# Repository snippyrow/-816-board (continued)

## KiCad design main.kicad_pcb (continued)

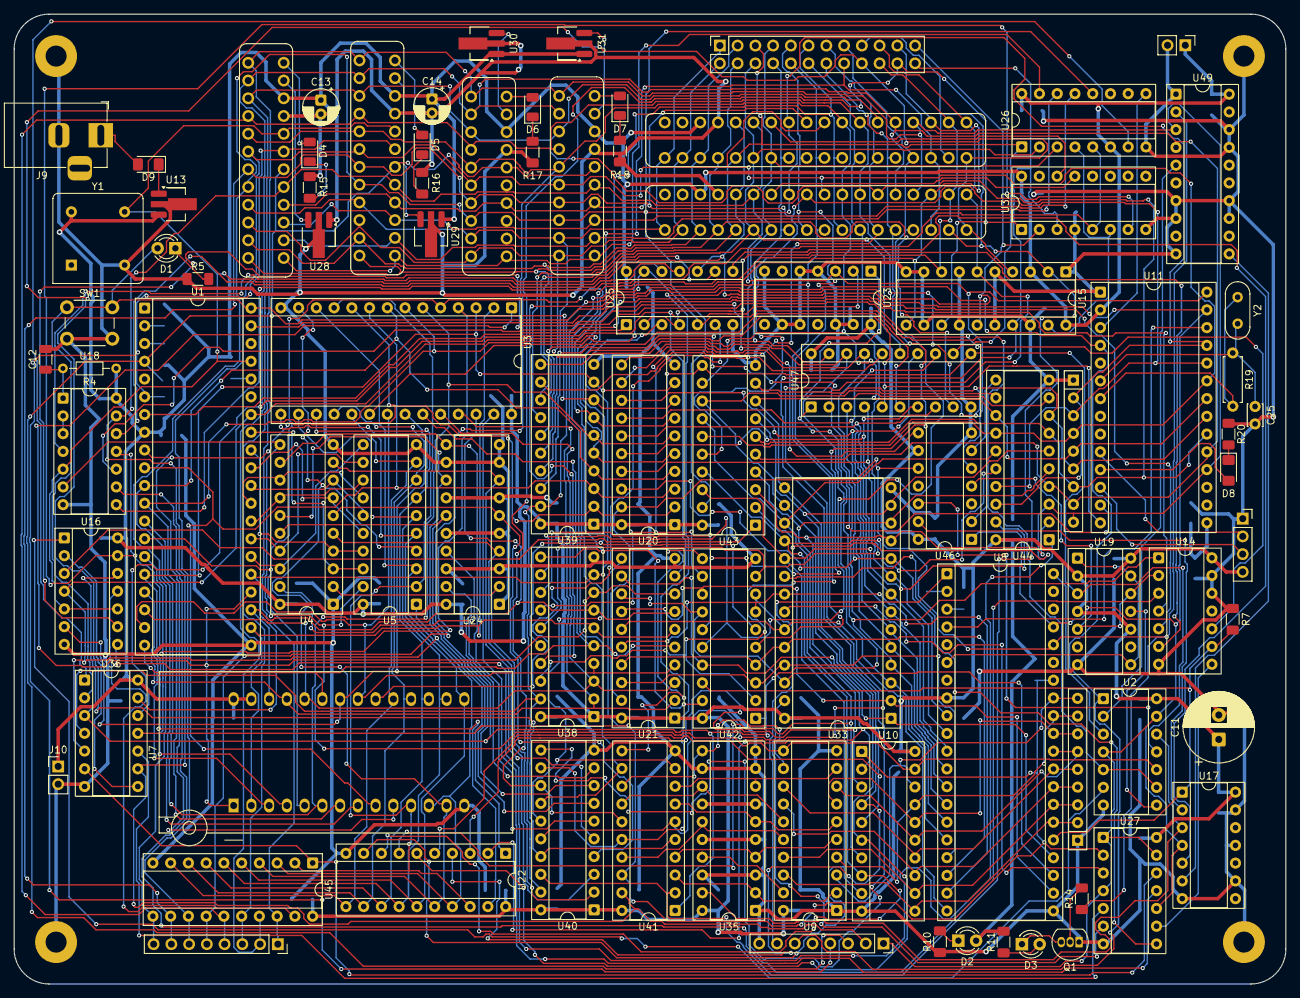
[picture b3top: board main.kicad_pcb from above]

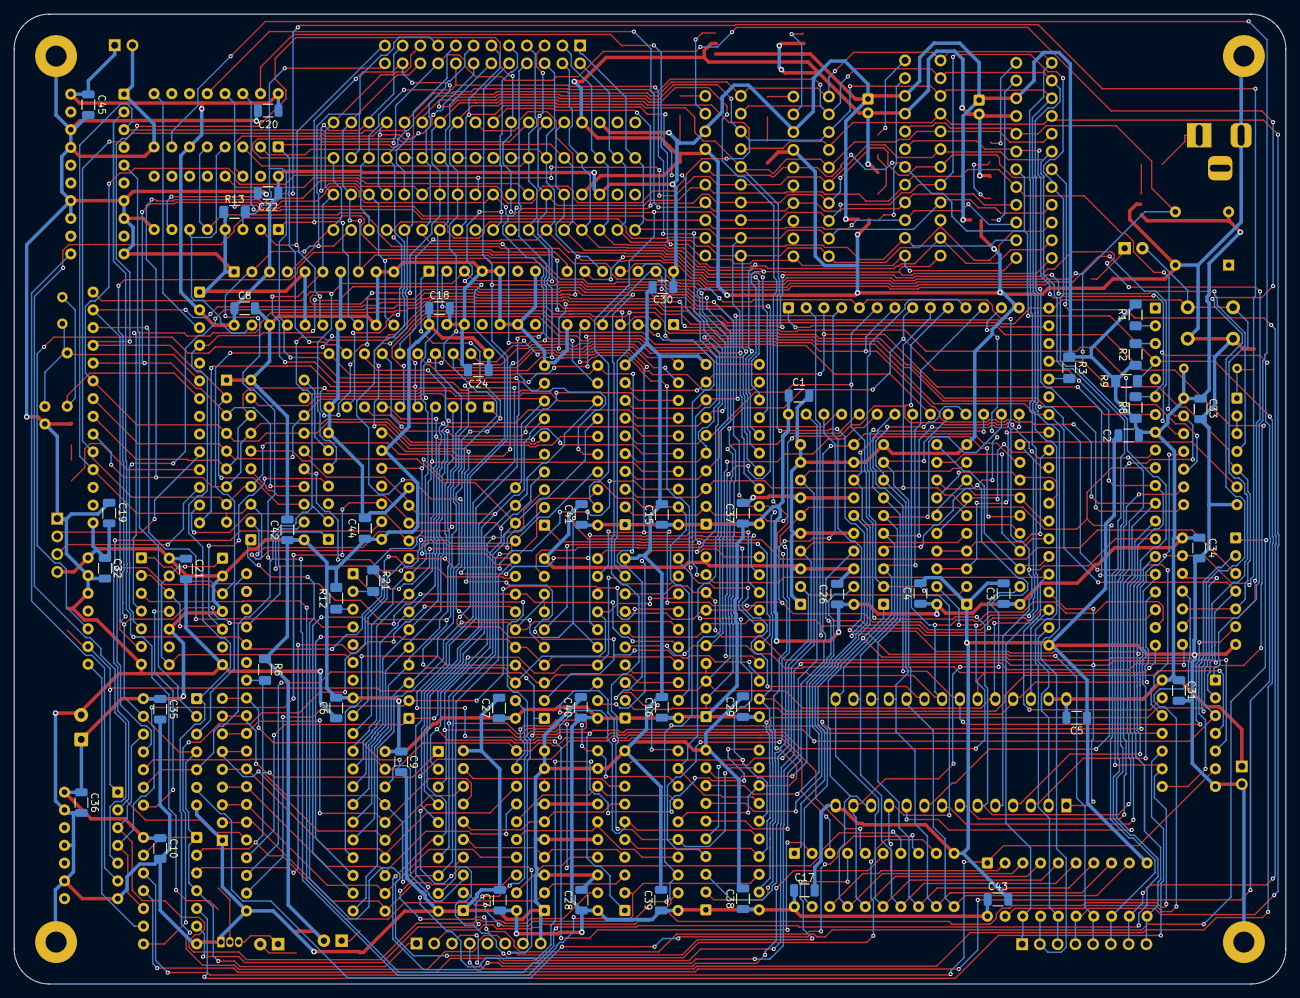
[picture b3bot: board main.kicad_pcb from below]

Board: 2 copper layers, 182.0 x 138.8 mm, 141 parts (48 on the bottom side), 206 nets.

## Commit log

2025-06-25 Rename main.kicad_pcb to OLD/main.kicad_pcb
2025-06-25 Rename main.kicad_pro to OLD/main.kicad_pro
2025-06-25 Rename main.kicad_sch to OLD/main.kicad_sch
